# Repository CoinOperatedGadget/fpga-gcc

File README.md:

# fpga-gcc
A FPGA Powered Gamecube Controller

This project is about using an FPGA in order to create a gamecube controller.  Most commonly microcontrollers are currently used for this purpose, so why use and FPGA?  Well there isn't a good reason other than I thought it would be a fun weekend project.  

I ended up building up a full controller:

## Features
- WASD style directional input on the left with 3 modifier keys, one for pinky use, 2 for thumb use
- Dedicated start button
- 8 button right cluster
- 5 button cluster for right thumb
- Per key addressable RGB
- Hot swap Mx style switches

The controller utilizes a Sipeed Tang Nano 4K board for control.  The top level for the instantiation can be found in the directory of the same name. 

GCC emulator code based on information found here:
- https://simplecontrollers.bigcartel.com/gamecube-protocol
- http://www.int03.co.uk/crema/hardware/gamecube/gc-control.html

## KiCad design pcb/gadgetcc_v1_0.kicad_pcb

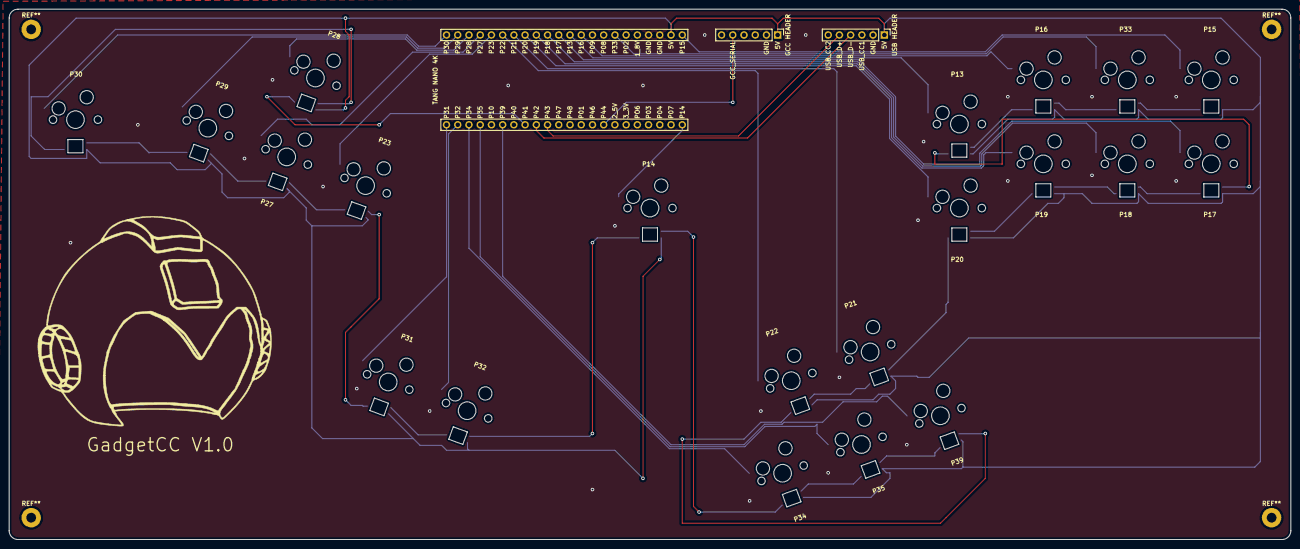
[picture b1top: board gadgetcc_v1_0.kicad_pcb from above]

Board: 2 copper layers, 290.0 x 120.0 mm, 45 parts (0 on the bottom side), 47 nets.

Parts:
FPGA1: Tang_nano_4K
GCC HEADER: PinHeader_1x06_P2.54mm_Vertical
LED1, LED2, LED3, LED4, LED5, LED6, LED7, LED8, LED9, LED10, LED11, LED12, LED13, LED14, LED15, LED16, LED17, LED18, LED19, LED20, LED21: SK6812-MINI-E
S1, S2, S3, S4, S5, S6, S7, S8, S9, S10, S11, S12, S13, S14, S15, S16, S17, S18, S19, S20, S21: MX
USB HEADER: PinHeader_1x06_P2.54mm_Vertical

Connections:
GND: FPGA1.19, FPGA1.20, GCC HEADER.2, LED1.3, LED2.3, LED3.3, LED4.3, LED5.3, LED6.3, LED7.3, LED8.3, LED9.3, LED10.3, LED11.3, LED12.3, LED13.3, LED14.3, LED15.3, LED16.3, LED17.3, LED18.3, LED19.3, LED20.3, LED21.3, S1.2, S2.2, S3.2, S4.2, S5.2, S6.2, S7.2, S8.2, S9.2, S10.2, S11.2, S12.2, S13.2, S14.2, S15.2, S16.2, S17.2, S18.2, S19.2, S20.2, S21.2, USB HEADER.2
P13: FPGA1.12, S9.1
P14: FPGA1.23, S21.1
P15: FPGA1.22, S15.1
P16: FPGA1.13, S11.1
P17: FPGA1.11, S14.1
P18: FPGA1.10, S12.1
P19: FPGA1.9, S10.1
P20: FPGA1.8, S8.1
P21: FPGA1.7, S20.1
P22: FPGA1.6, S18.1
P23: FPGA1.5, S5.1
P27: FPGA1.4, S3.1
P28: FPGA1.3, S4.1
P29: FPGA1.2, S2.1
P30: FPGA1.1, S1.1
P31: FPGA1.44, S6.1
P32: FPGA1.43, S7.1
P33: FPGA1.16, S13.1
P34: FPGA1.42, S16.1
P35: FPGA1.41, S17.1
P39: FPGA1.39, S19.1
P41: FPGA1.37, LED4.4
P42: FPGA1.36, USB HEADER.4
P43: FPGA1.35, USB HEADER.5
P44: FPGA1.30, GCC HEADER.5
S1: LED1.4, LED4.2
S2: LED1.2, LED2.4
S3: LED2.2, LED3.4
S4: LED3.2, LED5.4
S5: LED5.2, LED6.4
S6: LED6.2, LED7.4
S7: LED7.2, LED21.4
S8: LED16.4, LED21.2
S9: LED16.2, LED17.4
S10: LED17.2, LED19.4
S11: LED18.4, LED19.2
S12: LED18.2, LED20.4
S13: LED8.4, LED20.2
S14: LED8.2, LED10.4
S15: LED10.2, LED12.4
S16: LED12.2, LED14.4
S17: LED9.4, LED14.2
S18: LED9.2, LED11.4
S19: LED11.2, LED13.4
S20: LED13.2, LED15.4
VCC: FPGA1.21, GCC HEADER.1, LED1.1, LED2.1, LED3.1, LED4.1, LED5.1, LED6.1, LED7.1, LED8.1, LED9.1, LED10.1, LED11.1, LED12.1, LED13.1, LED14.1, LED15.1, LED16.1, LED17.1, LED18.1, LED19.1, LED20.1, LED21.1, USB HEADER.1

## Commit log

2022-09-22 Initial commit of controllers and top level for tang nano 4k
2022-10-11 Adding changes after creating first prototype, GadgetCC V1.0
2022-10-19 Adding LED Controller for adjustable per key RGB
    Initial commit of feature. Currently implemented in registers, should pipeline it and put it in block ram to save resources. Also TODO: Save to external flash on 4k Nano board (for the future...)
2022-10-28 Adding comments throughout file
